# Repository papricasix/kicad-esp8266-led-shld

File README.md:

# kicad-esp8266-led-shld
Schema and PCB design for a ESP8266 "shield"

## PCB shot (not assembled):

## PCB layout:

## PCB 3D preview (front & back):

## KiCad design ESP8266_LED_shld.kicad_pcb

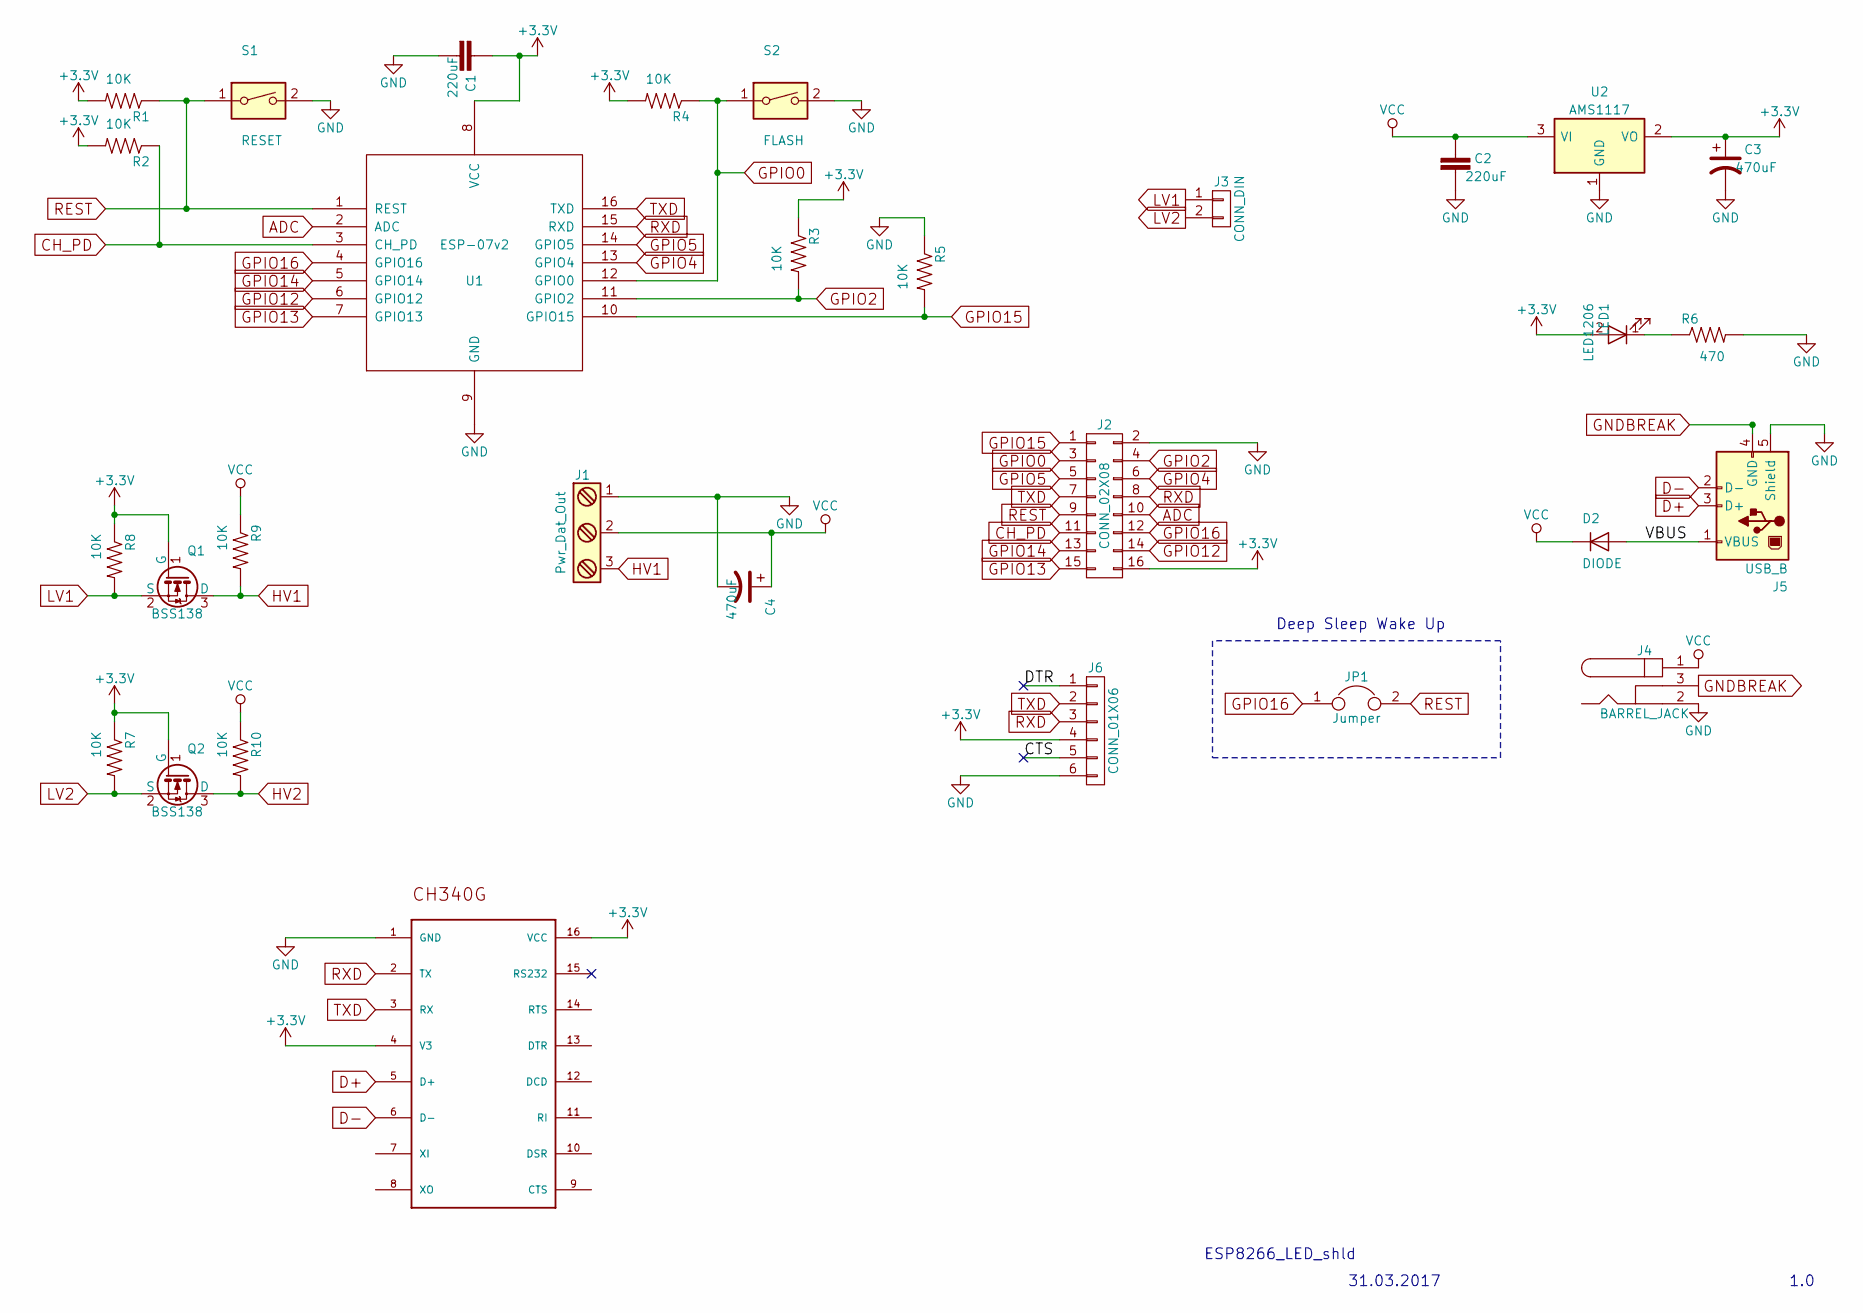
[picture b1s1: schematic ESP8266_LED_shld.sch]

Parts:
C1, C2: 220uF; C_1206_HandSoldering
C3, C4: 470uF; CP_Elec_8x10
D2: DIODE; D_SOD-323_HandSoldering
J1: Pwr_Dat_Out; TerminalBlock_Pheonix_MKDS1.5-3pol
J2: CONN_02X08; Pin_Header_Straight_2x08_Pitch2.54mm
J3: CONN_DIN; Pin_Header_Straight_1x02_Pitch2.54mm
J4: BARREL_JACK; BARREL_JACK-revision2
J5: USB_B; USB_Mini-B
J6: CONN_01X06; Pin_Header_Straight_1x06_Pitch2.54mm
JP1: Jumper; Pin_Header_Straight_1x03_Pitch2.54mm
LED1: LED1206; LED_1206-revision2
Q1, Q2: BSS138; SOT-23
R1, R2, R3, R4, R5, R7, R8, R9, R10: 10K; R_1206_HandSoldering
R6: 470; R_1206_HandSoldering
S1: RESET; SW_PUSH_6mm
S2: FLASH; SW_PUSH_6mm
U1: ESP-07v2
U2: AMS1117; SOT-223-3Lead_TabPin2

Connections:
+3V3: C1.1, C3.1, J2.16, J6.4, LED1.2 (A), Q1.1 (G), Q2.1 (G), R1.2, R2.2, R3.1, R4.2, R7.1, R8.1, U1.8 (VCC), U2.2 (VO); also elsewhere on the board
/CTS: J6.5
/DTR: J6.1
/VBUS: D2.2 (A), J5.1 (VBUS)
ADC: J2.10, U1.2 (ADC)
CH_PD: J2.11, R2.1, U1.3 (CH_PD)
GNDBREAK: J4.3, J5.4 (GND)
GPIO0: J2.3, R4.1, S2.1, U1.12 (GPIO0)
GPIO2: J2.4, R3.2, U1.11 (GPIO2)
GPIO4: J2.6, U1.13 (GPIO4)
GPIO5: J2.5, U1.14 (GPIO5)
GPIO12: J2.14, U1.6 (GPIO12)
GPIO13: J2.15, U1.7 (GPIO13)
GPIO14: J2.13, U1.5 (GPIO14)
GPIO15: J2.1, R5.2, U1.10 (GPIO15)
GPIO16: J2.12, JP1.1, U1.4 (GPIO16)
HV1: J1.3, Q1.3 (D), R9.2
HV2: Q2.3 (D), R10.2
LV1: J3.1, Q1.2 (S), R8.2
LV2: J3.2, Q2.2 (S), R7.2
unnamed: LED1.1 (K), R6.1
REST: J2.9, JP1.2, R1.1, S1.1, U1.1 (REST)
RXD: J2.8, J6.3, U1.15 (RXD)
TXD: J2.7, J6.2, U1.16 (TXD)
VCC: C2.1, C4.1, D2.1 (K), J1.2, J4.1, R9.1, R10.1, U2.3 (VI); also elsewhere on the board

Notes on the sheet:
1.0
31.03.2017
ESP8266_LED_shld
Deep Sleep Wake Up

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
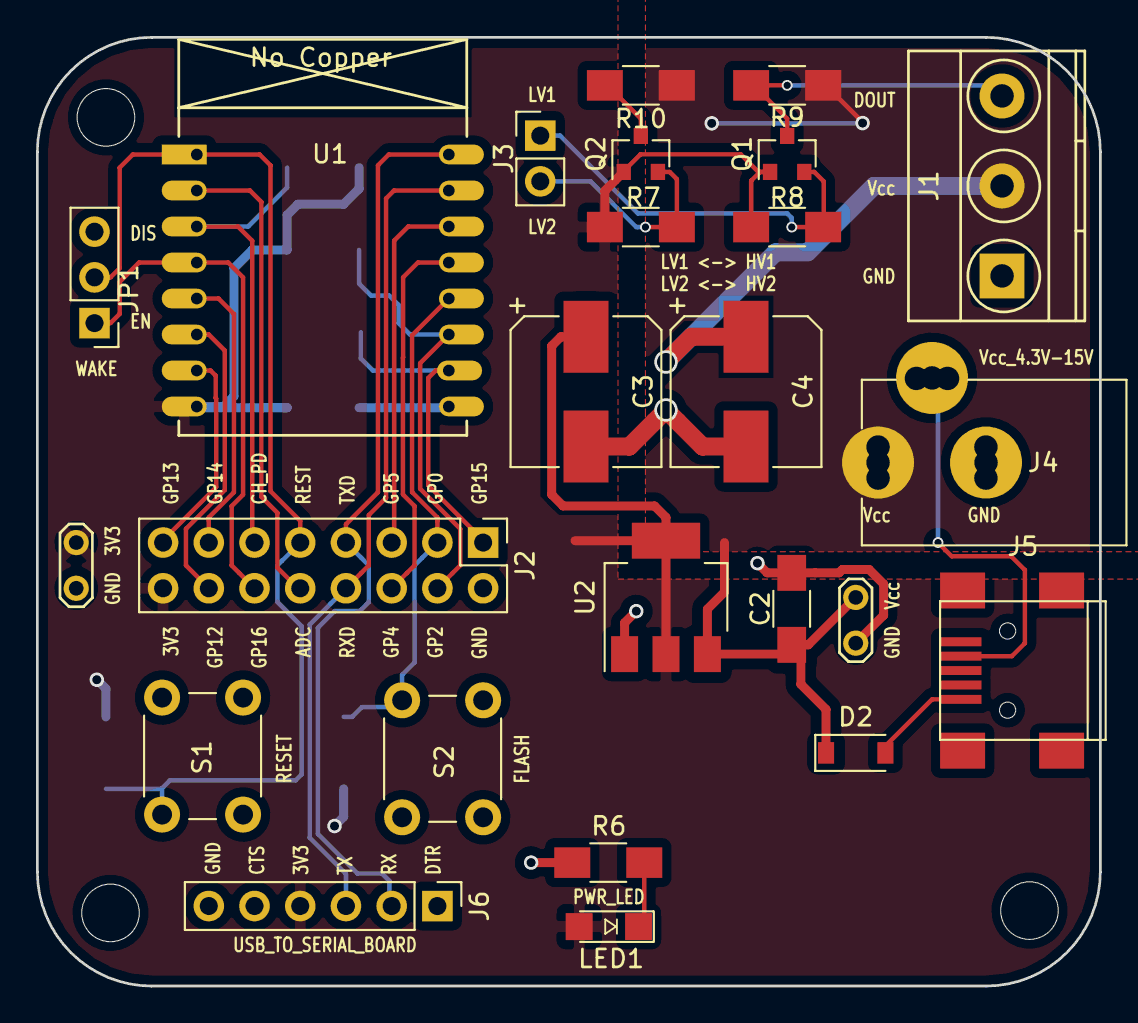
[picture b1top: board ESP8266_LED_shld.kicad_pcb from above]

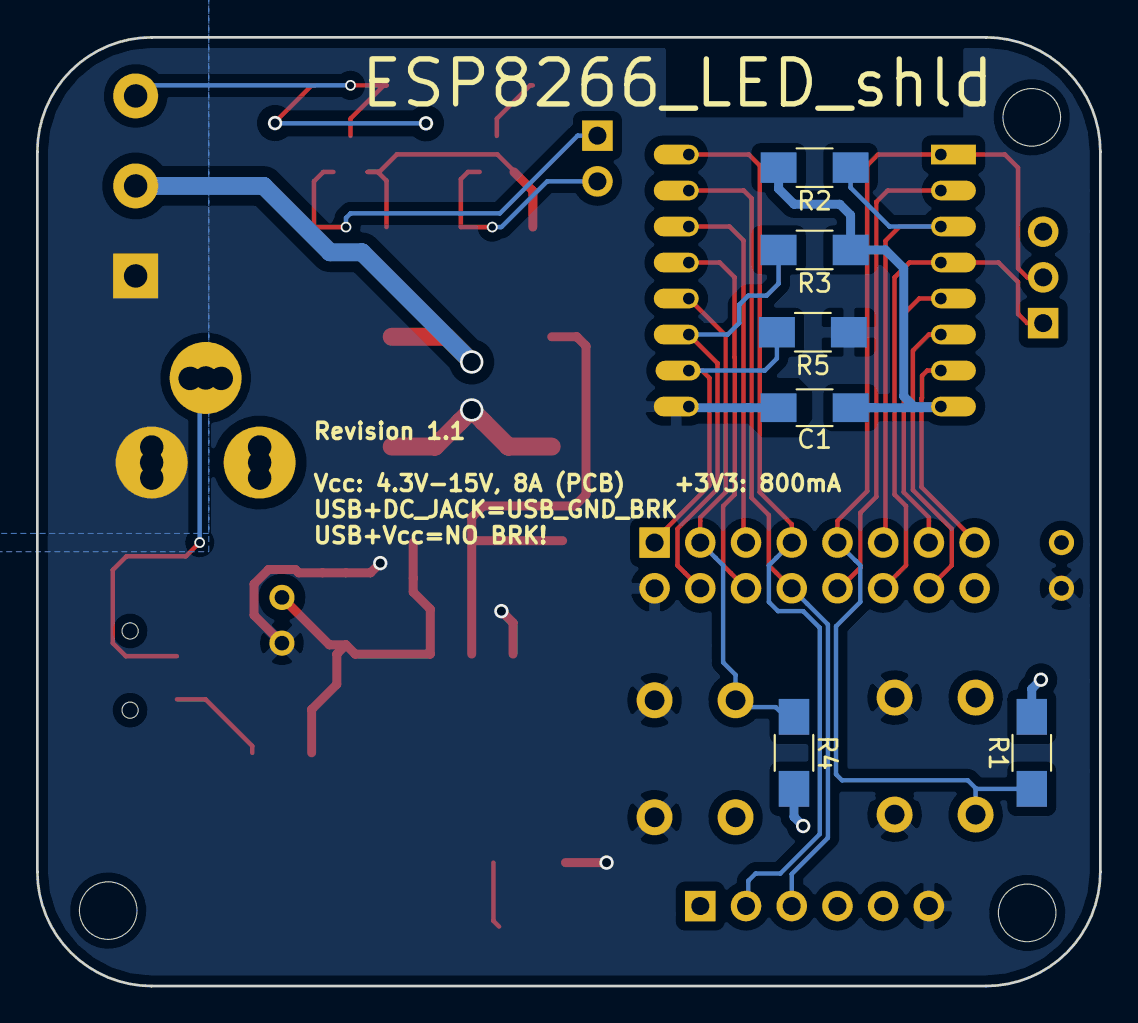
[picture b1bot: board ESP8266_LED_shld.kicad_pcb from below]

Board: 2 copper layers, 59.1 x 52.7 mm, 34 parts (6 on the bottom side), 24 nets.

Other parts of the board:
MH1, MH2, MH2#2: MountingHole_3.2mm_M3
T1, T1#2: Test_Point_2Pads

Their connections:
+3V3: T1#2.1; also elsewhere on the board
VCC: T1.1; also elsewhere on the board

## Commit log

2017-04-05 initial version 1.0 (sent to fab)
2017-04-05 added resistor between DOUT and HV4 to protect data pin of LED stip and fixed some silk screen labels (positions)
2017-04-06 Update LICENSE
    Added project name and author info
2017-04-08 added images for readme.md
2017-04-08 updated PCB design
2017-04-08 Create README.md
    initial readme check-in
2017-04-13 added pcb shot
2017-04-20 work started on rev2 [wip]
2017-04-21 changed usb micro b to usb mini b & added CH340G IC. some changes to PCB.
2017-04-24 minor changes (still wip)
